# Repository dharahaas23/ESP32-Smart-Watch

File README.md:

# ESP32 Smart Watch

A round, wrist-worn smart watch built around the ESP32-WROOM-32, with heart-rate sensing, a circular color display, USB-C charging, and a custom PCB antenna — designed as part of the #30DaysOfPCB progression from beginner to advanced boards.

## Overview

| | |
|---|---|
| **MCU** | ESP32-WROOM-32 |
| **Display** | GC9A01, round TFT (SPI) |
| **Heart-rate sensor** | MAX30102 (I2C) |
| **Charger / protection** | TP4056 + DW01A + FS8205A dual MOSFET |
| **Regulator** | AMS1117-3.3 |
| **USB / programming** | USB-C, CH340K USB-to-TTL bridge |
| **Board shape** | Circular, with a keep-out zone and PCB trace antenna for the ESP32 |
| **Layers** | 4-layer (F.Cu, In1.Cu, In2.Cu, B.Cu) |
| **Pads / Vias / Track segments** | 227 / 78 / 306 |
| **Nets** | 68 (fully routed — 0 unrouted) |

## Features

- **ESP32-WROOM-32** as the main controller, with dedicated `RESET`, `EN`, `BOOT`, and `Button` GPIOs
- **GC9A01 round display** driven over SPI, with separate SDA/SCL/RST/DC/CS lines
- **MAX30102** heart-rate/SpO2 sensor on I2C, footprint placed close to the skin-contact edge for optimal readings
- **USB-C** input for power and CH340K-based UART programming (TXD/RXD/DTR/RTS wired to EN/BOOT for auto-reset)
- **TP4056** single-cell Li-ion charge management with **DW01A + FS8205A** battery protection (over-charge/discharge/current)
- **On/off slide switch** and separate **BOOT** and **Function** push buttons
- **Custom PCB trace antenna** for the ESP32, isolated behind a defined keep-out zone
- Battery connector (BAT+ / BAT−) for a coin/pouch cell

## Design Notes

- Front copper is heavily used for power distribution and the ESP32 antenna keep-out; back copper carries the bulk of signal routing.
- The board silkscreen calls out `PLACE CLOSE TO THE SKIN` next to the MAX30102 footprint as a placement reminder for future revisions/enclosure design.
- Bottom silk includes maker/GitHub branding (`GitHub:dharahaas23`) and a "Designed with KiCad" mark.

## Tools

- **KiCad 10.0.1** — schematic capture, PCB layout, and 3D visualization

## Author

**S. Dharahaas**
GitHub: [@dharahaas23](https://github.com/dharahaas23)

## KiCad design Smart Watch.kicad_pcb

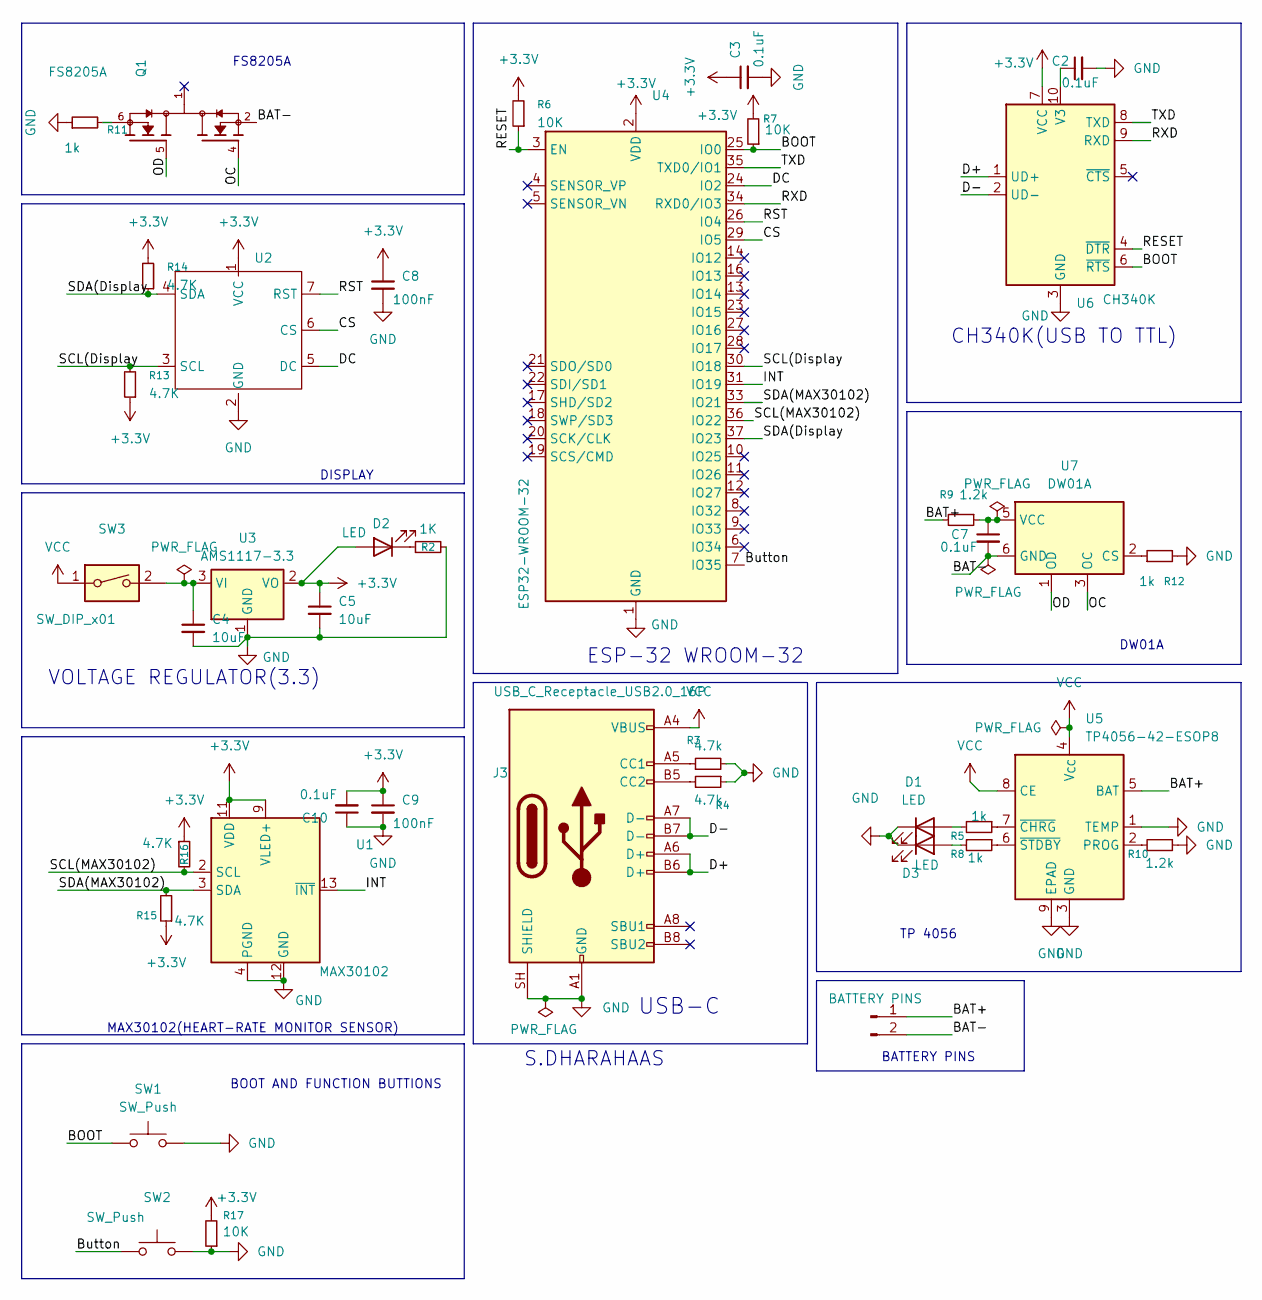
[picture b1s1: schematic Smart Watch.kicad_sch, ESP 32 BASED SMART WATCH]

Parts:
C2, C3, C7, C10: 0.1uF; C_0603_1608Metric
C4, C5: 10uF; C_0603_1608Metric
C8, C9: 100nF; C_0603_1608Metric
D1, D2, D3: LED; R_0805_2012Metric
J2: BATTERY PINS; JST_EH_S2B-EH_1x02_P2.50mm_Horizontal
J3: USB_C_Receptacle_USB2.0_16P; USB_C_Receptacle_HRO_TYPE-C-31-M-12
Q1: FS8205A; SOP65P640X120-8N; PARTREV 1.7
R2: 1K; R_0805_2012Metric
R3, R4: 4.7k; R_0805_2012Metric
R5, R8, R11, R12: 1k; R_0805_2012Metric
R6, R7, R17: 10K; R_0805_2012Metric
R9, R10: 1.2k; R_0805_2012Metric
R13, R14, R15, R16: 4.7K; R_0805_2012Metric
SW1, SW2: SW_Push; SW_SPST_TS-1088-xR025
SW3: SW_DIP_x01; SW_SPDT_PCM12
U1: MAX30102; Maxim_OLGA-14_3.3x5.6mm_P0.8mm
U2: Round display(mini)
U3: AMS1117-3.3; SOT-223-3_TabPin2
U4: ESP32-WROOM-32
U5: TP4056-42-ESOP8; SOIC-8-1EP_3.9x4.9mm_P1.27mm_EP2.41x3.3mm_ThermalVias
U6: CH340K; SSOP-10-1EP_3.9x4.9mm_P1mm_EP2.1x3.3mm
U7: DW01A; SOT-23-6

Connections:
+3.3V: C3.1, C5.1, C8.1, C9.1, C10.2, D2.2 (A), R6.2, R7.2, R13.1, R14.2, R15.1, R16.1, R17.2, U1.9 (VLED+), U1.10 (VLED+), U1.11 (VDD), U2.1 (VCC), U3.2 (VO), U4.2 (VDD), U6.7 (VCC)
/BAT+: J2.1, R9.2, U5.5 (BAT)
/BAT-: C7.2, J2.2, Q1.2, Q1.3, U7.6 (GND)
/BOOT: R7.1, SW1.1, U4.25 (IO0), U6.6 (~RTS)
/Button: SW2.1, U4.7 (IO35)
/CS: U2.6 (CS), U4.29 (IO5)
/D+: J3.A6 (D+), J3.B6 (D+), U6.1 (UD+)
/D-: J3.A7 (D-), J3.B7 (D-), U6.2 (UD-)
/DC: U2.5 (DC), U4.24 (IO2)
/INT: U1.13 (~INT), U4.31 (IO19)
/OC: Q1.4, U7.3 (OC)
/OD: Q1.5, U7.1 (OD)
/RESET: R6.1, U4.3 (EN), U6.4 (~DTR)
/RST: U2.7 (RST), U4.26 (IO4)
/RXD: U4.34 (RXD0/IO3), U6.9 (RXD)
/SCL(Display: R13.2, U2.3 (SCL), U4.30 (IO18)
/SCL(MAX30102): R16.2, U1.2 (SCL), U4.36 (IO22)
/SDA(Display: R14.1, U2.4 (SDA), U4.37 (IO23)
/SDA(MAX30102): R15.2, U1.3 (SDA), U4.33 (IO21)
/TXD: U4.35 (TXD0/IO1), U6.8 (TXD)
GND: C2.2, C3.2, C4.2, C5.2, C8.2, C9.2, C10.1, D1.1 (K), D3.1 (K), J3.A1 (GND), J3.A12 (GND), J3.B1 (GND), J3.B12 (GND), J3.SH (SHIELD), R2.2, R3.2, R4.1, R10.1, R11.1, R12.2, R17.1, SW1.2, SW2.2, U1.4 (PGND), U1.12 (GND), U2.2 (GND), U3.1 (GND), U4.1 (GND), U4.15 (GND), U4.38 (GND), U4.39 (GND), U5.1 (TEMP), U5.3 (GND), U5.9 (EPAD), U6.3 (GND), U6.11 (GND)
unnamed: D1.2 (A), R5.2
unnamed: D2.1 (K), R2.1
unnamed: D3.2 (A), R8.2
unnamed: J3.A5 (CC1), R3.1
unnamed: J3.B5 (CC2), R4.2
unnamed: Q1.6, Q1.7, R11.2
unnamed: C4.1, SW3.2, U3.3 (VI)
unnamed: R10.2, U5.2 (PROG)
unnamed: R5.1, U5.7 (~CHRG)
unnamed: R8.1, U5.6 (~STDBY)
unnamed: C2.1, U6.10 (V3)
unnamed: R12.1, U7.2 (CS)
unnamed: C7.1, R9.1, U7.5 (VCC)
VCC: J3.A4 (VBUS), J3.A9 (VBUS), J3.B4 (VBUS), J3.B9 (VBUS), SW3.1, U5.4 (V_{CC}), U5.8 (CE)

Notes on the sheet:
DW01A
FS8205A
MAX30102(HEART-RATE MONITOR SENSOR)
S.DHARAHAAS
CH340K(USB TO TTL)
BOOT AND FUNCTION BUTTIONS
TP 4056
BATTERY PINS
ESP-32 WROOM-32
DISPLAY
VOLTAGE REGULATOR(3.3)
USB-C

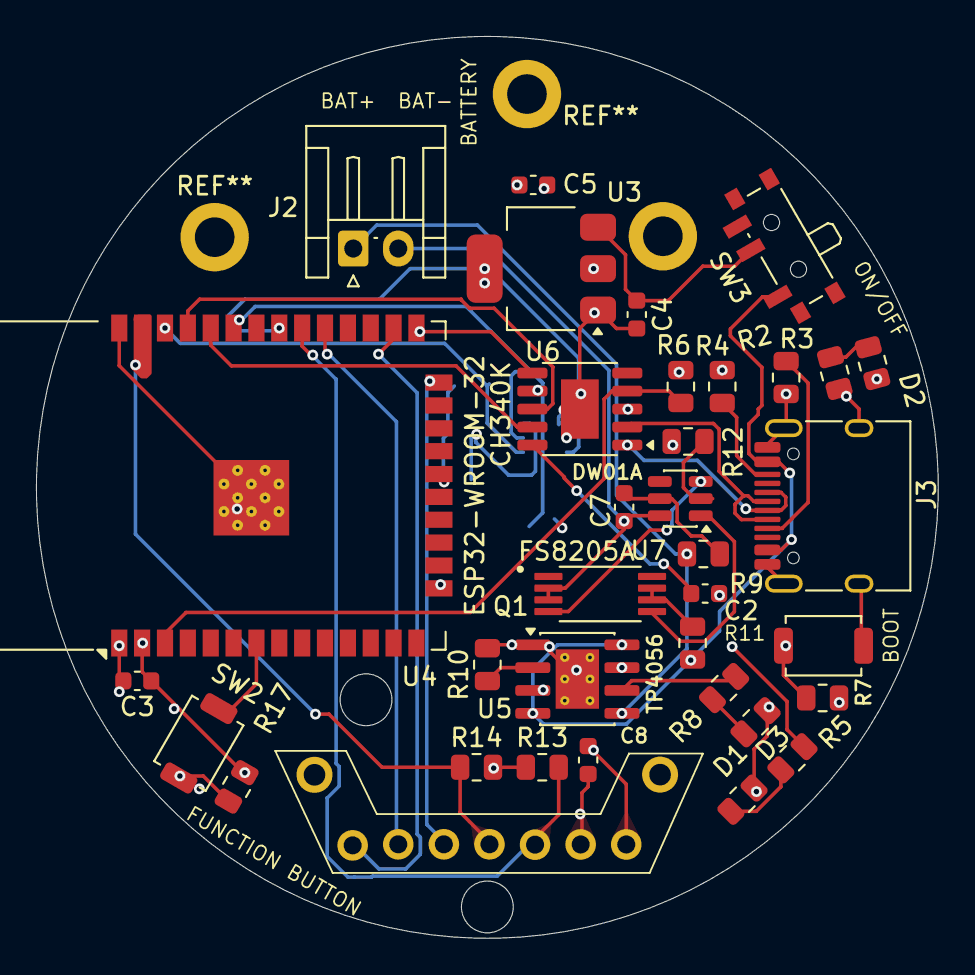
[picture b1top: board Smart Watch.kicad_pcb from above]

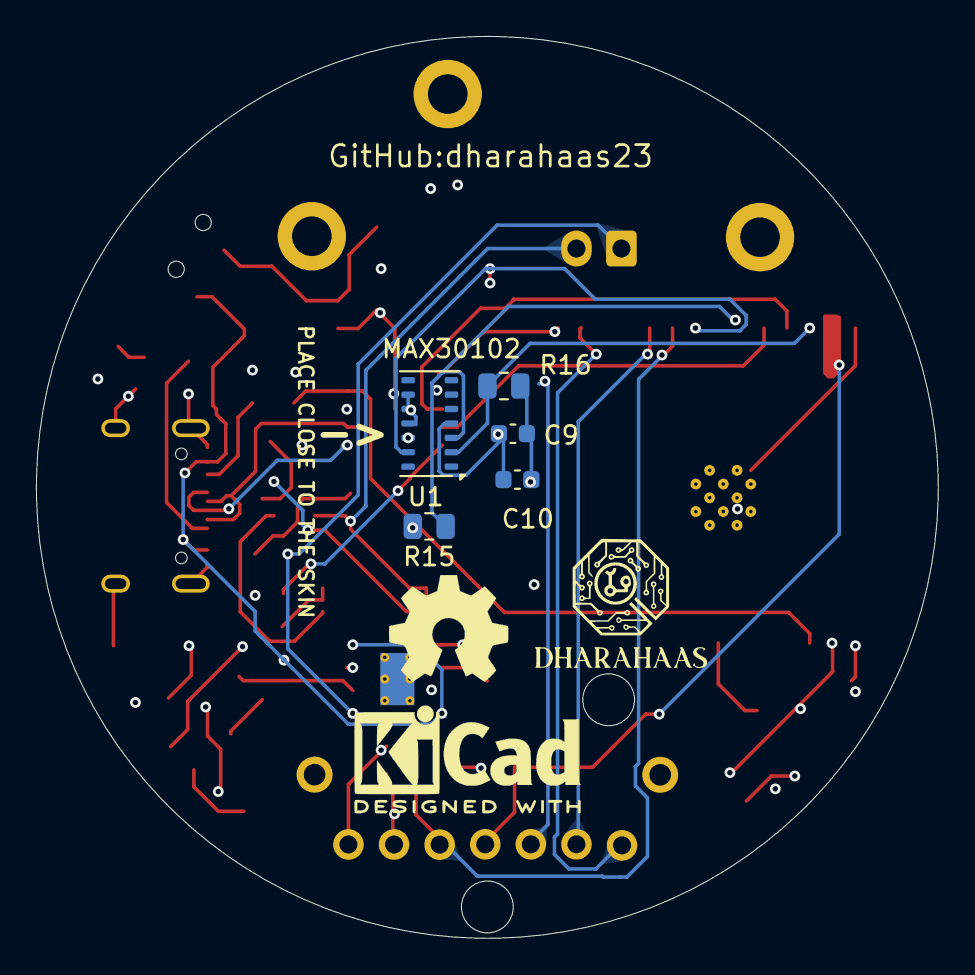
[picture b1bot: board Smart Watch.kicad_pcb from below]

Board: 4 copper layers, 50.1 x 50.1 mm, 40 parts (5 on the bottom side), 35 nets.
